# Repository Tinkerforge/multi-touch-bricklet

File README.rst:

Multi Touch Bricklet
====================

This repository contains the firmware source code and the hardware design
files. The documentation generator configs can be found at
https://github.com/Tinkerforge/generators

Repository Content
------------------

software/:
 * examples/: Examples for all supported languages
 * build/: Compiled files
 * src/: Source code of firmware
 * Makefile: Makefile to build project

hardware/:
 * Contains KiCad project files and additionally schematics as PDF

datasheets/:
 * Contains datasheets for sensors and complex ICs that are used

Hardware
--------

The hardware is designed with the open source EDA Suite KiCad
(http://www.kicad.org). Before you are able to open the files,
you have to install the Tinkerforge kicad-libraries
(https://github.com/Tinkerforge/kicad-libraries). You can either clone
them directly in hardware/ or clone them in a separate folder and
symlink them into hardware/
(ln -s kicad_path/kicad-libraries project_path/hardware). After that you
can open the .pro file in hardware/ with KiCad and from there view and
modify the schematics and the PCB layout.

Software
--------

If you want to do your own Brick/Bricklet firmware development we highly
recommend that you use our build environment setup script and read the
tutorial (https://www.tinkerforge.com/en/doc/Tutorials/Tutorial_Build_Environment/Tutorial.html).

To compile the C code we recommend you to install the newest GNU Arm Embedded
Toolchain (https://launchpad.net/gcc-arm-embedded/+download).
You also need to install bricklib (https://github.com/Tinkerforge/bricklib)
and brickletlib (https://github.com/Tinkerforge/brickletlib).

You can either clone it directly in software/src/ or clone it in a
separate folder and symlink it into software/src/
(ln -s bricklib_path/bricklib project_path/software/src/ and
ln -s brickletlib_path/brickletlib project_path/software/src/).
Finally make sure to have CMake installed
(http://www.cmake.org/cmake/resources/software.html).

After that you can build the firmware by invoking make in software/.
The firmware (.bin) can then be found in software/build/ and uploaded
with brickv (click button "Flashing" on start screen).

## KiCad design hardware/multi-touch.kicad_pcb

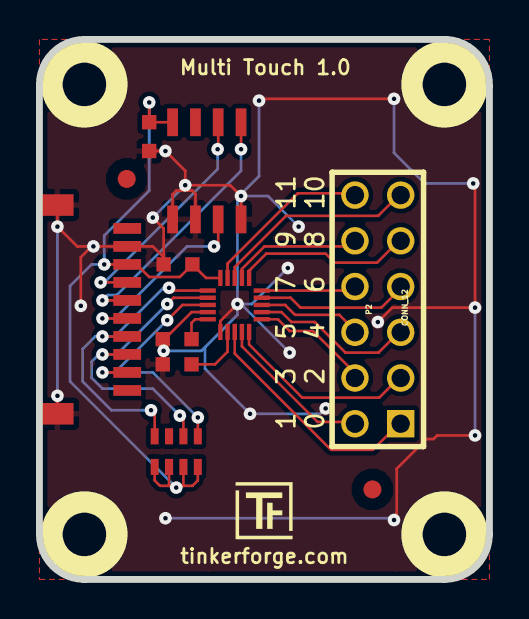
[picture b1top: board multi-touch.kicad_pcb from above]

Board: 2 copper layers, 25.0 x 30.0 mm, 17 parts (0 on the bottom side), 22 nets.

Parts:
C1, C2, C3: 100nF; C0603
Fiducial_Mark: VAL**; Fiducial_Mark
Fiducial_Mark#2: VAL**; Fiducial_Mark
P1: CON-SENSOR
P2: CONN_12; pin_array_6x2
R1: 75k; R0603
RP1: 10k; 0603X4
U1: M24C64; SOIC8
U2: MPR121Q; QFN20-3X3
U3, U4, U5, U6: DRILL; DRILL_NP
VAL: WEEE_7mm
VAL#2: CE_5mm

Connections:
GND: C1.2, C2.1, C3.1, P1.2, P1.EP, R1.2, U1.1, U1.2, U1.4, U2.4, U2.6
unnamed: C3.2, U2.5
unnamed: P1.4, U1.6
unnamed: P1.5, U1.5
unnamed: P1.6, U1.3
unnamed: P1.7, RP1.4, U2.1
unnamed: P1.8, RP1.2, U2.2
unnamed: P1.9, RP1.1, U2.3
unnamed: P2.1, U2.8
unnamed: P2.2, U2.9
unnamed: P2.3, U2.10
unnamed: P2.4, U2.11
unnamed: P2.5, U2.12
unnamed: P2.6, U2.13
unnamed: P2.7, U2.14
unnamed: P2.8, U2.15
unnamed: P2.9, U2.16
unnamed: P2.10, U2.17
unnamed: P2.11, U2.18
unnamed: P2.12, U2.19
unnamed: R1.1, U2.7
VCC: C1.1, C2.2, P1.3, RP1.5, RP1.6, RP1.7, RP1.8, U1.8, U2.20

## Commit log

2013-07-31 Initial commit for Multi Touch Bricklet
2013-07-31 Add prototype disclaimer to readme
2013-07-31 Remove debug code
2013-08-21 windows: Don't trigger a build in generate_makefile.bat
    Also use normal make instead of a special named one.
2013-08-30 Add API to enable/disable electrodes and recalibration
2013-09-17 Add examples for Multi Touch Bricklet
2013-09-20 ruby: Fix indentation
2013-09-20 Fix typo
2013-10-15 add hardware
2013-10-18 Fix name to fit naming standard
2013-10-31 Add Get/SetSensitivity API
2014-01-06 Add static assert for BrickContext size
2014-01-10 Add Perl examples
2014-01-15 php: Use const for constant values
2014-02-07 Add Mathematica examples
2014-02-10 perl: fixed namespace
2014-02-12 javascript: add examples
2014-02-18 javascript: examples fixed
2014-02-20 javascript: add html examples
2014-02-24 javascript: port 4280, startExample()
2014-02-28 javascript: Break long lines and cleanup whitespace
2014-03-05 Add LabVIEW examples
2014-03-06 labview: Add examples in LV2010 format
2014-03-31 perl: Fix whitespace
2014-03-31 matlab: add examples
2014-04-02 java: Unify constants style
2014-04-02 perl: Unify print style
2014-04-17 matlab: Adapt examples to new callback style
2014-04-17 matlab: Add parentheses to make pygments happy
2014-07-15 java: Replace System.console() usage with an Eclipse compatible pattern
2014-12-02 Use ReadLine instead of ReadKey for C# example
2015-02-13 vbnet: Use ReadLine instead of ReadKey
    Because ReadKey doesn't work with a pipe as stdin on the RED Brick.
2015-03-02 windows: Stop cmake from searching for mingw32-make.exe
    Using MinGW Makefiles as generator makes cmake search for mingw32-make.exe
    which might not be installed because GnuWin32's make.exe is used instead.
2015-04-09 c: Whitespace
2015-06-23 matlab: Simplify string handling
2015-07-25 Make JavaScript browser example textarea readonly
2015-07-27 Cleanup C/C++, C#, Java and Python examples
2015-07-29 Reformat changelog
2015-08-07 Use full device class name in Python examples
2015-08-12 Fix minor warnings in C/C++ examples
2015-08-18 Fix error in C/C++ examples
2015-08-18 Cleanup VB.NET examples
2015-08-18 Fix complie errors in C/C++ examples
2015-08-19 Cleanup Perl examples
2015-09-09 Duplicate cmake call to fix bug during cmake creation
2015-09-25 drc run, change drills to np
2015-09-25 fix fiducials
2015-10-05 Generator based example cleanup
2015-11-12 matlab: Fix callback handling for R2014a
    http://undocumentedmatlab.com/blog/matlab-callbacks-for-java-events-in-r2014a
2015-11-12 Fix typos
2015-11-25 Include date and commit into changelog
2016-02-10 Remove bogus comment
2016-05-18 c: Add missing device destroy call
2016-07-01 Make the change UID comment more explicit
2017-04-13 csharp: Adapt example
2017-06-02 octave: Use javaObject instead of deprecated java_new
2017-11-30 Update examples from generator
2017-12-07 mathematica: Also generate .nb files
2017-12-12 Add 3d information
2018-02-19 javascript: Close div tag correctly
2018-02-20 Cleanup KiCad libraries config
    Ensure LibDir=kicad-libraries and LibName1=tinkerforge.
    Remove special library.
2018-05-11 Rename files
2018-05-24 perl: Use strict in examples
2018-07-11 Add Makefile with docker support
2018-07-11 Update directory structure and build instructions
2018-07-11 Remove obsolete generate_makefile scripts
2018-11-06 Add rust examples
2018-11-07 rust: Accept host names for ip connection, fix naming inconsistencies
2018-11-07 rust: Rename callback receivers.
2018-12-14 Add go examples.
2018-12-18 go: Change import path.
2018-12-18 go: Change import path again.
2018-12-20 rust: Reformat examples.
2019-01-24 mqtt: Add examples.
2019-01-24 mqtt: Remove executable bit in example permissions.
2019-01-24 go: Minor example fixes.
2019-03-11 fixed library and schematic
2019-08-22 c: Adapt to bindings changes
2020-01-14 examples: Use python3 input by default.
2020-03-17 Whitespace
2020-03-17 rust: Update to new skeleton
2020-04-07 examples: rust: Print result string.
2021-10-25 Update KiCad link
    https://www.kicad.org/blog/2021/10/Avoid-links-to-former-kicad-domain/
2021-12-15 Make sure set_electrode_sensitivity returns if response expected
2021-12-15 Fix 2.0.1 revision
2022-07-06 Add license files.

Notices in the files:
hardware/multi-touch.kicad_pcb:
Licensed under CERN OHL v.1.1
Copyright (©) 2013, B.Nordmeyer
Copyright Tinkerforge GmbH 2013.
This documentation describes Open Hardware and is licensed under the
CERN OHL v. 1.1.
